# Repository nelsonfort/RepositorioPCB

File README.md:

# RepositorioPCB
# RepositorioPCB

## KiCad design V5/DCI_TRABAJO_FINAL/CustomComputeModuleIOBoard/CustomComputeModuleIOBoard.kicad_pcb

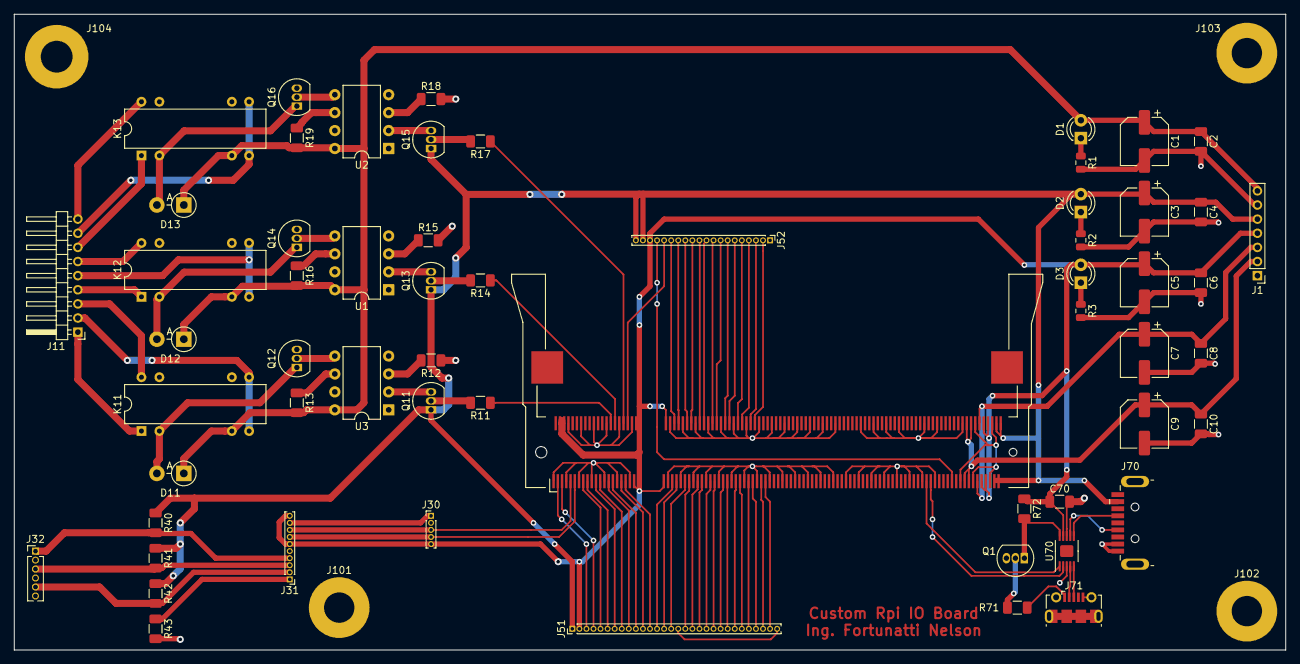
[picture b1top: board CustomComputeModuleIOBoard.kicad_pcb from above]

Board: 2 copper layers, 180.0 x 90.0 mm, 63 parts (0 on the bottom side), 97 nets.

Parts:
C1, C3, C5, C7, C9: 100uF; CP_Elec_6.3x3
C2, C4, C6, C8, C10, C70: 100nF; C_1206_3216Metric
D1: Red; LED_D3.0mm_IRBlack
D2: Green; LED_D3.0mm_IRBlack
D3: Blue; LED_D3.0mm_IRBlack
D11, D12, D13: 1N4007; D_DO-41_SOD81_P3.81mm_Vertical_AnodeUp
J1: DC INPUT; PinHeader_1x07_P2.00mm_Vertical
J11: Relay Output; PinHeader_1x09_P2.00mm_Horizontal
J20: SODIMM-200ForRpi; ConnectorFootprintSodimm200
J30: RTC Module; PinHeader_1x05_P1.00mm_Vertical
J31: ADS1115 Module; PinHeader_1x10_P1.00mm_Vertical
J32: Pt100-INPUT; PinHeader_1x06_P1.27mm_Vertical
J51: Conector_GPIO_0_27; PinHeader_1x30_P1.00mm_Vertical
J52: Conector_GPIO_28_45; PinHeader_1x20_P1.00mm_Vertical
J70: USB_A; USB3_A_Plug_Wuerth_692112030100_Horizontal
J71: USB_B_Micro; USB_Micro-B_Molex-105017-0001
J101, J102, J103: Conn_01x01; MountingHole_4.3mm_M4_Pad
J104: Conn_01x01; MountingHole_4.5mm_Pad
K11, K12, K13: DIPxx-1Cxx-51x; Relay_StandexMeder_DIP_LowProfile
Q1, Q11, Q12, Q13, Q14, Q15, Q16: BC337; TO-92_Inline
R1: 680; R_0805_2012Metric
R2: 220; R_0805_2012Metric
R3: 82; R_0805_2012Metric
R11, R14, R17: 330; R_1206_3216Metric
R12, R15, R18: 120; R_1206_3216Metric
R13, R16, R19, R40, R41, R42: 3300; R_1206_3216Metric
R43: 10000; R_1206_3216Metric
R71: 510; R_1206_3216Metric
R72: 47K; R_1206_3216Metric
U1, U2, U3: 6N136; DIP-8_W7.62mm
U70: FSUSB42UMX; MSOP-10-1EP_3x3mm_P0.5mm_EP1.68x1.88mm

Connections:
+1V8: C9.1, C10.1, J1.2, J20.183, J20.184, J20.185, J20.186
+2V5: C7.1, C8.1, J1.3, J20.189, J20.190
+3V3: C5.1, C6.1, C70.1, D3.2, J1.4, J20.4, J20.6, J20.39, J20.40, J20.41, J20.42, J20.191, J20.192, J20.193, J20.194, J30.5, J31.6, J31.10, J51.2, J52.18, R72.1, U70.9
+5V: C3.1, C4.1, D2.2, J1.5, J20.197, J20.198, J20.199, J20.200, J51.1, J52.19, J52.20, J70.1, Q11.1, Q13.1, Q15.1, R40.1, R41.1, R42.1
+12V: C1.1, C2.1, D1.2, D11.1, D12.1, D13.1, J1.7, K11.6, K12.6, K13.6, R13.2, R16.2, R19.2, U1.8, U2.8, U3.8
/ADCyRTC/A0: J31.4, J32.1, R40.2
/ADCyRTC/A1: J31.3, J32.3, R41.2
/ADCyRTC/A2: J31.2, J32.5, R42.2
/ADCyRTC/A3: J31.1, R43.1
/GPIO-Connectors/GPIO0: J20.3, J51.3
/GPIO-Connectors/GPIO1: J20.5, J51.4
/GPIO-Connectors/GPIO4: J20.15, J51.5
/GPIO-Connectors/GPIO5: J20.17, J51.6
/GPIO-Connectors/GPIO6: J20.21, J51.7
/GPIO-Connectors/GPIO7: J20.23, J51.8
/GPIO-Connectors/GPIO8: J20.27, J51.9
/GPIO-Connectors/GPIO9: J20.29, J51.10
/GPIO-Connectors/GPIO10: J20.33, J51.11
/GPIO-Connectors/GPIO11: J20.35, J51.12
/GPIO-Connectors/GPIO12: J20.45, J51.13
/GPIO-Connectors/GPIO13: J20.47, J51.14
/GPIO-Connectors/GPIO14: J20.51, J51.15
/GPIO-Connectors/GPIO15: J20.53, J51.17
/GPIO-Connectors/GPIO16: J20.57, J51.18
/GPIO-Connectors/GPIO17: J20.59, J51.19
/GPIO-Connectors/GPIO18: J20.63, J51.20
/GPIO-Connectors/GPIO19: J20.65, J51.21
/GPIO-Connectors/GPIO20: J20.69, J51.22
/GPIO-Connectors/GPIO21: J20.71, J51.23
/GPIO-Connectors/GPIO22: J20.75, J51.24
/GPIO-Connectors/GPIO23: J20.77, J51.25
/GPIO-Connectors/GPIO24: J20.81, J51.26
/GPIO-Connectors/GPIO25: J20.83, J51.27
/GPIO-Connectors/GPIO26: J20.87, J51.28
/GPIO-Connectors/GPIO27: J20.89, J51.29
/GPIO-Connectors/GPIO31: J20.36, J52.16
/GPIO-Connectors/GPIO32: J20.46, J52.15
/GPIO-Connectors/GPIO33: J20.48, J52.14
/GPIO-Connectors/GPIO34: J20.52, J52.13
/GPIO-Connectors/GPIO35: J20.54, J52.12
/GPIO-Connectors/GPIO36: J20.58, J52.11
/GPIO-Connectors/GPIO37: J20.60, J52.10
/GPIO-Connectors/GPIO38: J20.64, J52.9
/GPIO-Connectors/GPIO39: J20.66, J52.8
/GPIO-Connectors/GPIO40: J20.70, J52.7
/GPIO-Connectors/GPIO41: J20.72, J52.6
/GPIO-Connectors/GPIO42: J20.76, J52.5
/GPIO-Connectors/GPIO43: J20.78, J52.4
/GPIO-Connectors/GPIO44: J20.82, J52.3
/GPIO-Connectors/GPIO45: J20.84, J52.2
/GPIO-Connectors/RUN: J20.177, J52.17
/HDMIyUSB/SEL: Q1.1, R72.2, U70.10
/HDMIyUSB/USB_DM: J20.167, U70.2
/HDMIyUSB/USB_DP: J20.165, U70.1
/HDMIyUSB/VIN_USB_SLAVE: J71.1, R71.2
/OptocouplerAndRelays/CompCOM: J11.2, K11.7, K11.8
/OptocouplerAndRelays/CompNA: J11.3, K11.14
/OptocouplerAndRelays/CompNC: J11.1, K11.1
/OptocouplerAndRelays/CompSignal: J20.28, R11.1
/OptocouplerAndRelays/ResCOM: J11.8, K13.7, K13.8
/OptocouplerAndRelays/ResNA: J11.9, K13.14
/OptocouplerAndRelays/ResNC: J11.7, K13.1
/OptocouplerAndRelays/VentCOM: J11.5, K12.7, K12.8
/OptocouplerAndRelays/VentNA: J11.6, K12.14
/OptocouplerAndRelays/VentNC: J11.4, K12.1
/raspberryModuleConnection/GPIO2: J20.9, J30.3, J31.8
/raspberryModuleConnection/GPIO3: J20.11, J30.4, J31.7
/raspberryModuleConnection/GPIO29: J20.30, R14.1
/raspberryModuleConnection/GPIO30: J20.34, R17.1
GND: C3.2, C4.2, C5.2, C6.2, C7.2, C8.2, C9.2, C10.2, C70.2, J1.1, J20.1, J20.7, J20.8, J20.13, J20.14, J20.19, J20.20, J20.25, J20.26, J20.31, J20.32, J20.37, J20.38, J20.43, J20.44, J20.49, J20.50, J20.55, J20.56, J20.61, J20.62, J20.67, J20.68, J20.73, J20.74, J20.79, J20.80, J20.85, J20.86, J20.91, J20.92, J20.97, J20.98, J20.103, J20.104, J20.109, J20.110, J20.115, J20.116, J20.121, J20.122, J20.127, J20.133, J20.134, J20.139, J20.140, J20.145, J20.146, J20.151, J20.152, J20.157, J20.163, J20.164, J20.169, J20.170, J20.181, J20.182, J20.187, J20.188, J20.195, J20.196, J30.1, J31.9, J32.2, J32.4, J32.6, J51.16, J51.30, J52.1, J70.4, J70.5, J71.5, J71.6, Q1.3, R2.2, R3.2, R12.1, R15.2, R18.2, R43.2, U70.3, U70.8
GNDPWR: C1.2, C2.2, J1.6, Q12.3, Q14.3, Q16.3, R1.2
unnamed: D1.1, R1.1
unnamed: D2.1, R2.1
unnamed: D3.1, R3.1
unnamed: D11.2, K11.2, Q12.1
unnamed: D12.2, K12.2, Q14.1
unnamed: D13.2, K13.2, Q16.1
unnamed: J70.2, U70.6
unnamed: J70.3, U70.7
unnamed: J71.2, U70.4
unnamed: J71.3, U70.5
unnamed: Q1.2, R71.1
unnamed: Q11.2, R11.2
unnamed: Q11.3, U3.2
unnamed: Q12.2, U3.5
unnamed: Q13.2, R14.2
unnamed: Q13.3, U1.2
unnamed: Q14.2, U1.5
unnamed: Q15.2, R17.2
unnamed: Q15.3, U2.2
unnamed: Q16.2, U2.5
unnamed: R12.2, U3.3
unnamed: R13.1, U3.6
unnamed: R15.1, U1.3
unnamed: R16.1, U1.6
unnamed: R18.1, U2.3
unnamed: R19.1, U2.6

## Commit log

2019-06-18 second commit
2019-06-26 fourth commit
    Schematic and PCB Completed
